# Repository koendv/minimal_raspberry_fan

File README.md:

# Minimal LTC1695 Raspberry Fan Controller

This is a small fan speed controller for the Raspberry Pi. The [schematic](doc/schematic.pdf) is just one ic and two capacitors. The whole board is just 16.0 x 24.0 mm (0.63 x 0.95 inches).

## Hardware
The github contains kicad project files and python script for raspbian. This is a link to the pcb as an orderable [shared project at oshpark](https://oshpark.com/shared_projects/uS7DB7dc), and these are the components as a [shared project at Mouser](https://www.mouser.com/ProjectManager/ProjectDetail.aspx?AccessID=1c164b36e2). 
The fan used is 5V DC, brushless, 2 wire, **1W max**.

## Bill of Materials

Quant.|Prod. No.|Description
---|---|---
1|LTC1695CS5|I2C Fan Speed Controller, SOT-23
2|KEMET T494B475K020AT|Tantalum Capacitor, SMD 20V 4.7uF 1311 10% ESR=1 Ohms
1|Molex 15-44-6806|female header, 2x03, 2.54mm pitch

## Installation
The fan controller plugs into pin 1-6 of the Raspberry GPIO. Enable i2c bus 1 clicking on the raspberry icon -> Preferences -> Raspberry Pi Configuration -> Interfaces -> i2c. If you scan the i2c bus, you ought to see the fan controller at address 0x74:
```
koen@raspberrypi:~ $ sudo i2cdetect -r -y 1
     0  1  2  3  4  5  6  7  8  9  a  b  c  d  e  f
00:          -- -- -- -- -- -- -- -- -- -- -- -- -- 
10: -- -- -- -- -- -- -- -- -- -- -- -- -- -- -- -- 
20: -- -- -- -- -- -- -- -- -- -- -- -- -- -- -- -- 
30: -- -- -- -- -- -- -- -- -- -- -- -- -- -- -- -- 
40: -- -- -- -- -- -- -- -- -- -- -- -- -- -- -- -- 
50: -- -- -- -- -- -- -- -- -- -- -- -- -- -- -- -- 
60: -- -- -- -- -- -- -- -- -- -- -- -- -- -- -- -- 
70: -- -- -- -- 74 -- -- --                         
koen@raspberrypi:~ $ 
```
You can switch the fan completely on:
```
i2cset -y 1 0x74 63
```
completely off:
```
i2cset -y 1 0x74 0
```
or something in between:
```
i2cset -y 1 0x74 32
```
At low speeds, the fan might need a little extra push to get going. If you add 64 to the speed the fan will run at full speed for 0.25s, then slow down to the programmed speed. As an example,
```
i2cset -y 1 0x74 84
```
runs the  fan at the full 5V for a quarter second to get the fan moving, then drops to 1.56V for normal operation.

Lastly, you can read the fan controller status:
```
i2cget -y 1 0x74 
```

Value | Status
--------|--------
0|ok
64|thermal shutdown (T > 155 degree C)
128|overcurrent (I > 390mA)
192|thermal shutdown *and* overcurrent

## Running

The ```raspbian``` directory contains [fanctl.py](raspbian/fanctl.py), a python script which you can run either interactively or in the background. 

variable|value|description
---|---|---
fan_min|21|minimum fan speed. fan will stall below fan_min.
fan_boost|25|fan_boost is the lowest speed where the fan will reliably begin to rotate. fan speeds below fan_boost need 0.25s at full voltage to get the fan moving first.
fan_max|63|maximum fan speed. 63 corresponds to full +5V.
temp_min|60|switch fan off below temp_min degrees
temp_max|80|run fan at full speed at temp_max or above

The values for *fan_min* and *fan_boost* are for the fan I'm using. The values  *temp_min* and *temp_max* represent personal choices. Once you are happy with the values, you can add the fan controller to ```/etc/rc.local``` so the fan starts up at boot:
```
/usr/local/bin/fanctl.py &
```

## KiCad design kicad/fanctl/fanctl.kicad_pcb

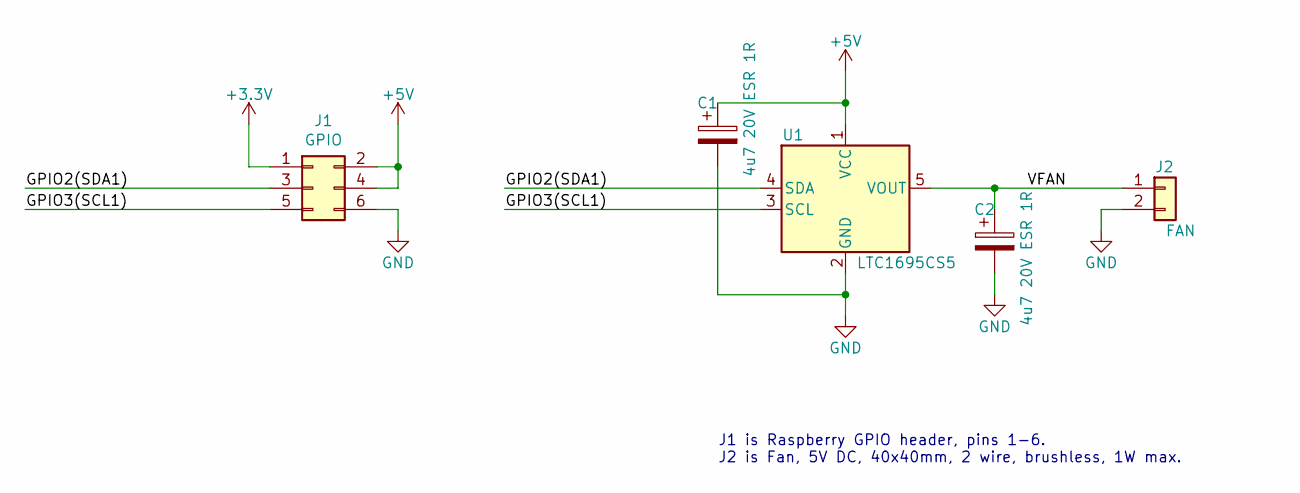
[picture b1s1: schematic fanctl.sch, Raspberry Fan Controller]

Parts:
C1, C2: 4u7 20V ESR 1R; CP_EIA-3528-12_Kemet-T_Pad1.50x2.35mm_HandSolder
J1: GPIO; PinSocket_2x03_P2.54mm_Vertical
J2: FAN; PinHeader_1x02_P2.54mm_Vertical
U1: LTC1695CS5; TSOT-23-5_HandSoldering

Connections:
+3V3: J1.1
+5V: C1.1, J1.2, J1.4, U1.1 (VCC)
/GPIO2(SDA1): J1.3, U1.4 (SDA)
/GPIO3(SCL1): J1.5, U1.3 (SCL)
/VFAN: C2.1, J2.1, U1.5 (VOUT)
GND: C1.2, C2.2, J1.6, J2.2, U1.2 (GND)

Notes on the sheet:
J1 is Raspberry GPIO header, pins 1-6. J2 is Fan, 5V DC, 40x40mm, 2 wire, brushless, 1W max.

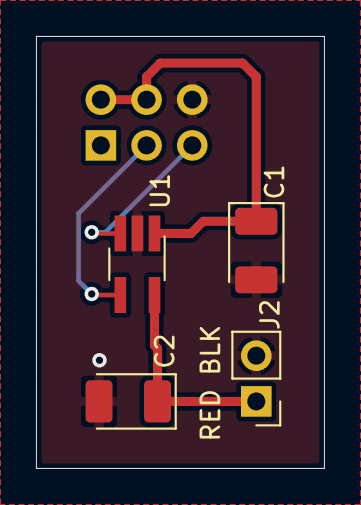
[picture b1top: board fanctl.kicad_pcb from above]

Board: 2 copper layers, 16.0 x 24.0 mm, 5 parts (1 on the bottom side), 5 nets.

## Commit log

2019-08-30 initial
2019-09-03 add temp
2019-09-04 script

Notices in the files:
kicad/fanctl/fanctl.kicad_pcb:
Released under the Creative Commons Attribution-ShareAlike 4.0 license.
